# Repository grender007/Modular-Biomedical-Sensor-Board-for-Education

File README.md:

# Modular-Biomedical-Sensor-Board-for-Education (MediBrick-2000)
Modular Biomedical Sensor Board for Education (a.k.a. MediBrick-2000), designed for the Department of Biomedical Engineering (BME) of the University of Arizona (UofA). The device currently integrates five different sensor for physiological measurements:

* [Skin Impedance](https://github.com/grender007/Modular-Biomedical-Sensor-Board-for-Education/tree/main/Skin%20Impedance%20Sensor)

* [Temperature](https://github.com/grender007/Modular-Biomedical-Sensor-Board-for-Education/tree/main/Temperature%20Sensor)

* [ECG](https://github.com/grender007/Modular-Biomedical-Sensor-Board-for-Education/tree/main/ECG%20Sensor%20)

* [Pulse Ox ](https://github.com/grender007/Modular-Biomedical-Sensor-Board-for-Education/tree/main/Pulse%20Ox%20Sensor)

* [Digital Stethoscope](https://github.com/grender007/Modular-Biomedical-Sensor-Board-for-Education/tree/main/Sound%20Sensor)

Each one of the folders include the Arduino Code (that also enables wireless communication), the PCB files, and the corresponding insert for the casing.

# Project Point Design
This is a wireless device mainly supported by ESPNow. Each one of the sensors has its own PCB and its own ESP32-S3 (see Arduino Code in any of the sensor folders). The signals are sent to a sixth ESP32-S3, [the receiver](https://github.com/grender007/Modular-Biomedical-Sensor-Board-for-Education/tree/main/ESP32%20Receiver), that simultaneously communicates with the user's computer through the [GUI](https://github.com/grender007/Modular-Biomedical-Sensor-Board-for-Education/tree/main/GUI). The GUI displays the measurements in real time and allows the user to record and save the information.

When not in use, the sensors can be placed on the charging station, where the batteries can be recharged.

# Sensor Modules
All the sensor modules are meant to be the same, being the only difference each sensor and the PCB that includes the required circuitry (But all the PCB have the same dimension and orientation). Each [sensor module](https://github.com/grender007/Modular-Biomedical-Sensor-Board-for-Education/tree/main/Housing%20Models/Module%20Casing) has different features. It includes an OLED screen that displays the current battery level and a button that allows the deep sleep mode of the ESP32-S3. The casing it is designed for the ESP32-S3 to be powered by a battery and to recharge with a magnetic plug.
All the modules can be placed on the [charging station](https://github.com/grender007/Modular-Biomedical-Sensor-Board-for-Education/tree/main/Housing%20Models/Charging%20Station) to recharge the batteries. Similarly, the receiver includes its own [casing](https://github.com/grender007/Modular-Biomedical-Sensor-Board-for-Education/tree/main/Housing%20Models/Receiver%20Casing).

# Assembly
The detailed asssembly process and the required parts for the device are described in the [Documents folder](https://github.com/grender007/Modular-Biomedical-Sensor-Board-for-Education/tree/main/User%20Manual%20and%20Other%20Documents), as well other related documents like the Technical Data Package (TDP).

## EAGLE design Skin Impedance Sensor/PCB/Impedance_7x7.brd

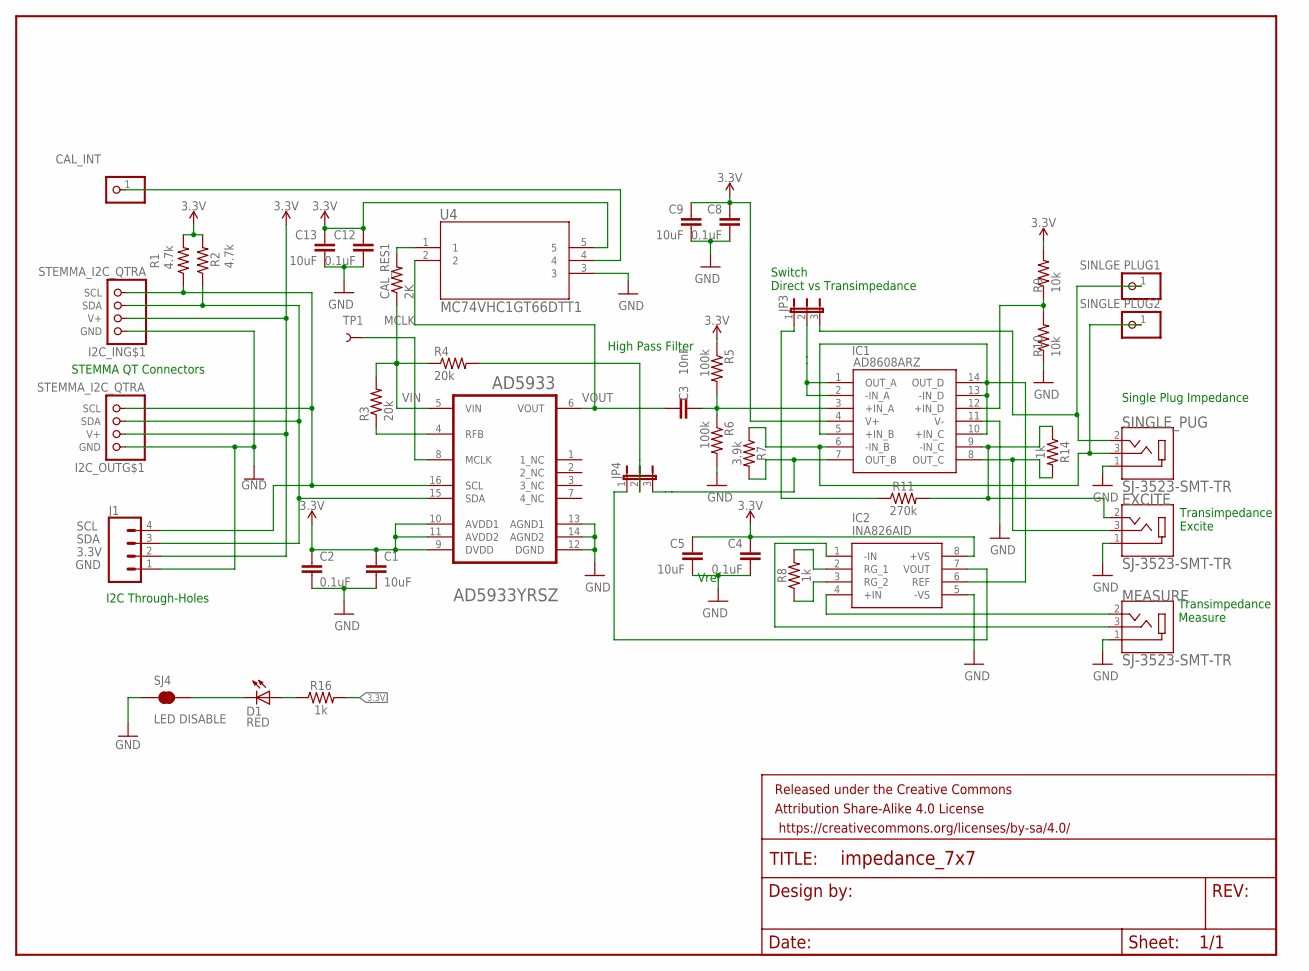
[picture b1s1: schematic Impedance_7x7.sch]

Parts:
AD5933: ANALOG_DEVICES_AD5933YRSZANALOG_DEVICES_AD5933YRS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; ANALOG_DEVICES_AD5933YRSZ_0
C1, C5, C9, C13: 10uF; C0603
C2, C4, C8, C12: 0.1uF; C0603
C3: 10nF; 0603
CAL_INT: PINHD-1X1; 1X01
CAL_RES1: 2K; R0603
D1: RED; LED-0603
EXCITE: SJ-3523-SMT-TR; CUI_SJ-3523-SMT-TR
FRAME1: FRAME-LETTERNO_PACKAGE; DUMMY
I2C_IN, I2C_OUT: STEMMA_I2C_QTRA; JST_SH4_RA
IC1: AD8608ARZ; SOIC127P600X175-14N
IC2: INA826AID; SOIC127P600X175-8N
J1: CONN_04; 1X04
JP3, JP4: JP2E; JP2
MEASURE: SJ-3523-SMT-TR; CUI_SJ-3523-SMT-TR
R1, R2: 4.7k; 0603
R3, R4: 20k; 0603
R5, R6: 100k; 0603
R7: 3.9k; 0603
R8, R14, R16: 1k; 0603
R9, R10: 10k; 0603
R11: 270k; 0603
SINGLE_PLUG1: SINLGE PLUG1; 1X01
SINGLE_PLUG2: SINGLE PLUG2; 1X01
SINGLE_PUG: SJ-3523-SMT-TR; CUI_SJ-3523-SMT-TR
SJ4: LED DISABLE; SMT-JUMPER_2_NC_TRACE_NO-SILK
TP1: TEST-POINT3X5; PAD.03X.05
U4: MC74VHC1GT66DTT1; TSOP5_1P65X3P15_ONS

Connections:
3.3V: AD5933.9 (DVDD), AD5933.10 (AVDD1), AD5933.11 (AVDD2), C1.1, C2.1, C4.1, C5.1, C8.1, C9.1, C12.1, C13.1, I2C_IN.2 (V+), I2C_OUT.2 (V+), IC1.4 (V+), IC2.8 (+VS), J1.2, R1.2, R2.2, R5.1, R9.2, R16.2, U4.5
GND: AD5933.12 (DGND), AD5933.13 (AGND1), AD5933.14 (AGND2), C1.2, C2.2, C4.2, C5.2, C8.2, C9.2, C12.2, C13.2, EXCITE.1, I2C_IN.1 (GND), I2C_OUT.1 (GND), IC1.11 (V-), IC2.5 (-VS), J1.1, MEASURE.1, R6.2, R10.1, SINGLE_PUG.1, SJ4.1, U4.3
MCLK: AD5933.8 (MCLK), TP1.P$1
unnamed: IC1.6 (-IN_B), R7.1, SINGLE_PLUG2.1, SINGLE_PUG.3
unnamed: CAL_INT.1, U4.4
unnamed: IC1.7 (OUT_B), JP4.3, R7.2
unnamed: JP4.2, R4.2
unnamed: AD5933.4 (RFB), R3.1
unnamed: C3.2, IC1.3 (+IN_A), R5.2, R6.1
unnamed: JP3.3, SINGLE_PLUG1.1, SINGLE_PUG.2
unnamed: JP3.1, R11.1
unnamed: IC1.1 (OUT_A), IC1.2 (-IN_A), JP3.2
unnamed: IC2.7 (VOUT), JP4.1
unnamed: IC1.12 (+IN_D), R9.1, R10.2
unnamed: IC1.5 (+IN_B), IC1.10 (+IN_C), IC1.13 (-IN_D), IC1.14 (OUT_D), IC2.6 (REF)
unnamed: EXCITE.2, IC1.9 (-IN_C), R11.2, R14.1
unnamed: IC2.4 (+IN), MEASURE.2
unnamed: IC2.1 (-IN), MEASURE.3
unnamed: IC2.2 (RG_1), R8.2
unnamed: IC2.3 (RG_2), R8.1
unnamed: CAL_RES1.2, U4.1
unnamed: EXCITE.3, IC1.8 (OUT_C), R14.2
unnamed: D1.A, R16.1
unnamed: D1.C, SJ4.2
SCL: AD5933.16 (SCL), I2C_IN.4 (SCL), I2C_OUT.4 (SCL), J1.4, R1.1
SDA: AD5933.15 (SDA), I2C_IN.3 (SDA), I2C_OUT.3 (SDA), J1.3, R2.1
VIN: AD5933.5 (VIN), CAL_RES1.1, R3.2, R4.1
VOUT: AD5933.6 (VOUT), C3.1, U4.2

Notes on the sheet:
High Pass Filter
Vref
Transimpedance Measure
Transimpedance Excite
Single Plug Impedance
STEMMA QT Connectors
I2C Through-Holes
Switch Direct vs Transimpedance

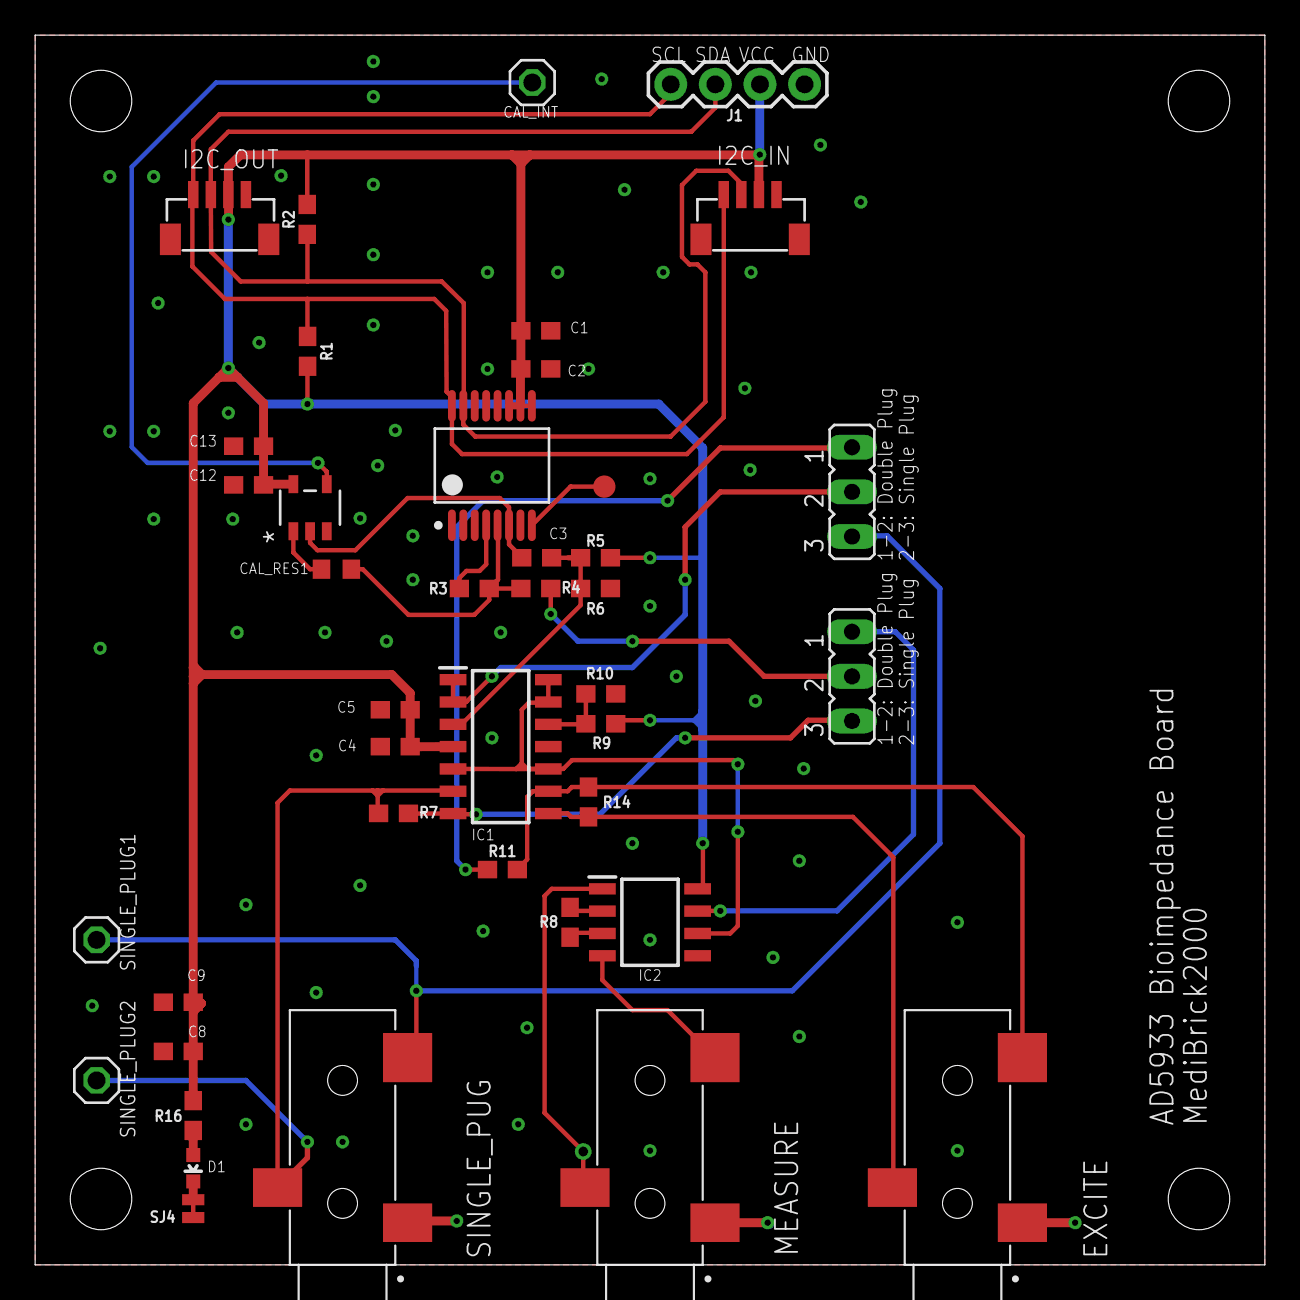
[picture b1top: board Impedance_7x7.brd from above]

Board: 2 copper layers, 70.0 x 70.0 mm, 42 parts (0 on the bottom side), 28 nets.

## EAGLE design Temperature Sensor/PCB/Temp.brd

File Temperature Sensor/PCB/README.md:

The temperature PCB is the simplest PCB of this project. It opperates using a simple wheatstone bridge, a parallel circuit composed of two branches, each with two resistors on each branch. One resistor is a thermistor, a resistor whose resistance changes with the temperature, serving as the probe for the project. As the temperature and thus resistance of the probe changes, the reading between the resistors of both branches will change. This difference in voltage is measured by the ESP32 and is used to calculate the temperature of the thermistor.

The PCB is also outfitted with a Red LED, allowing the User to see when the PCB has power.

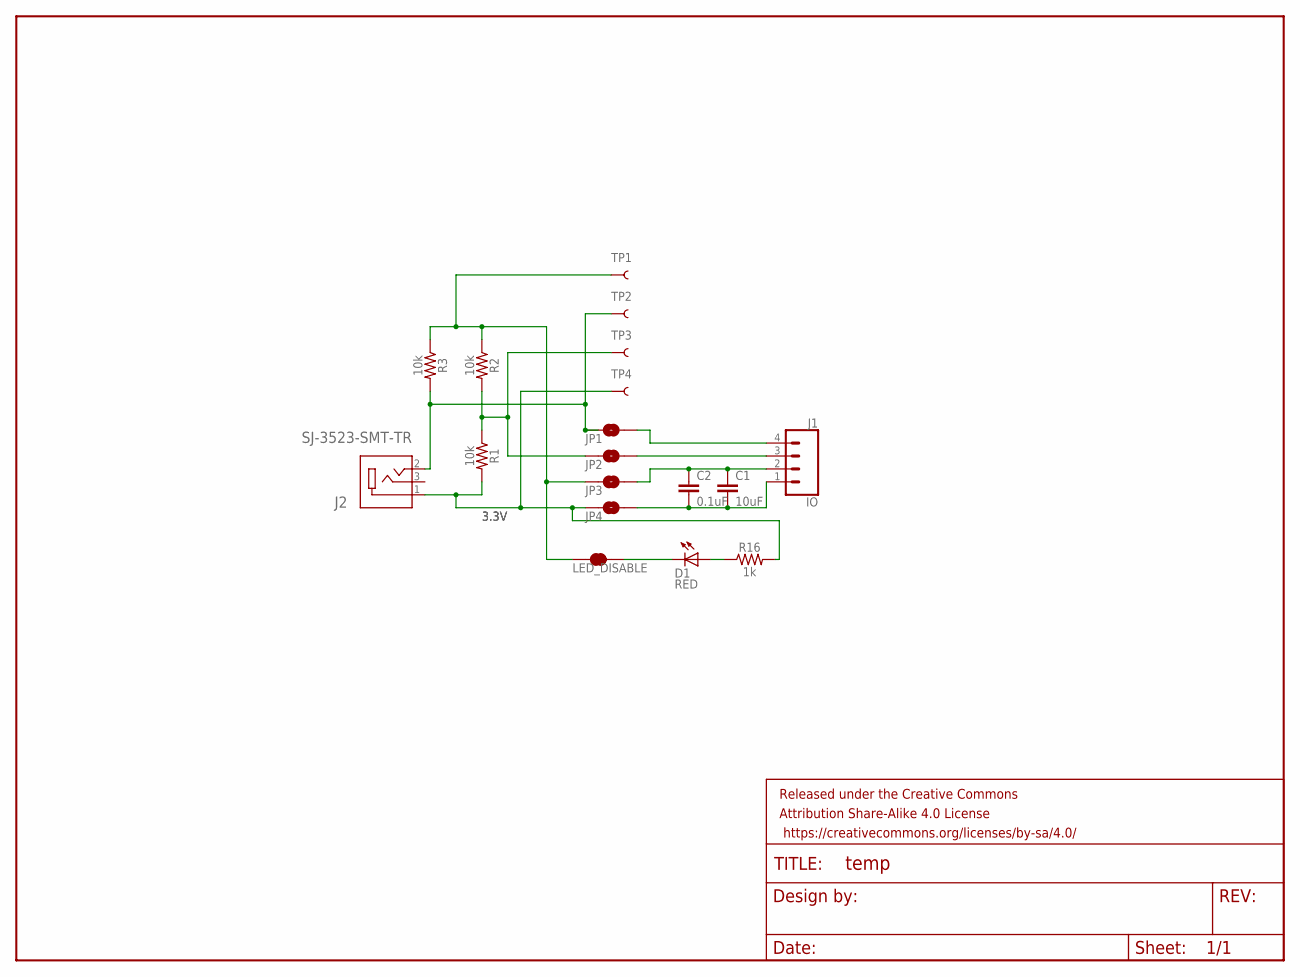
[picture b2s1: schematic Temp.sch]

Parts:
C1: 10uF; 0603
C2: 0.1uF; 0603
D1: RED; LED-0603
FRAME1: FRAME-LETTERNO_PACKAGE; DUMMY
J1: IO; 1X04
J2: SJ-3523-SMT-TR; CUI_SJ-3523-SMT-TR
JP1, JP2, JP3, JP4: JUMPER-SMT_2_NO_NO-SILK; SMT-JUMPER_2_NO_NO-SILK
LED_DISABLE: JUMPER-SMT_2_NC_TRACE_SILK; SMT-JUMPER_2_NC_TRACE_SILK
R1, R2, R3: 10k; 0603
R16: 1k; 0603
TP1, TP2, TP3, TP4: TEST-POINT3X5; PAD.03X.05

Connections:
3.3V: J2.1, JP4.1, R1.2, R16.2, TP4.P$1
unnamed: JP3.1, LED_DISABLE.1, R2.1, R3.1, TP1.P$1
unnamed: C1.2, C2.2, J1.1, JP4.2
unnamed: JP2.1, R1.1, R2.2, TP3.P$1
unnamed: C1.1, C2.1, J1.2, JP3.2
unnamed: J1.3, JP2.2
unnamed: J2.2, JP1.1, R3.2, TP2.P$1
unnamed: J1.4, JP1.2
unnamed: D1.A, R16.1
unnamed: D1.C, LED_DISABLE.2

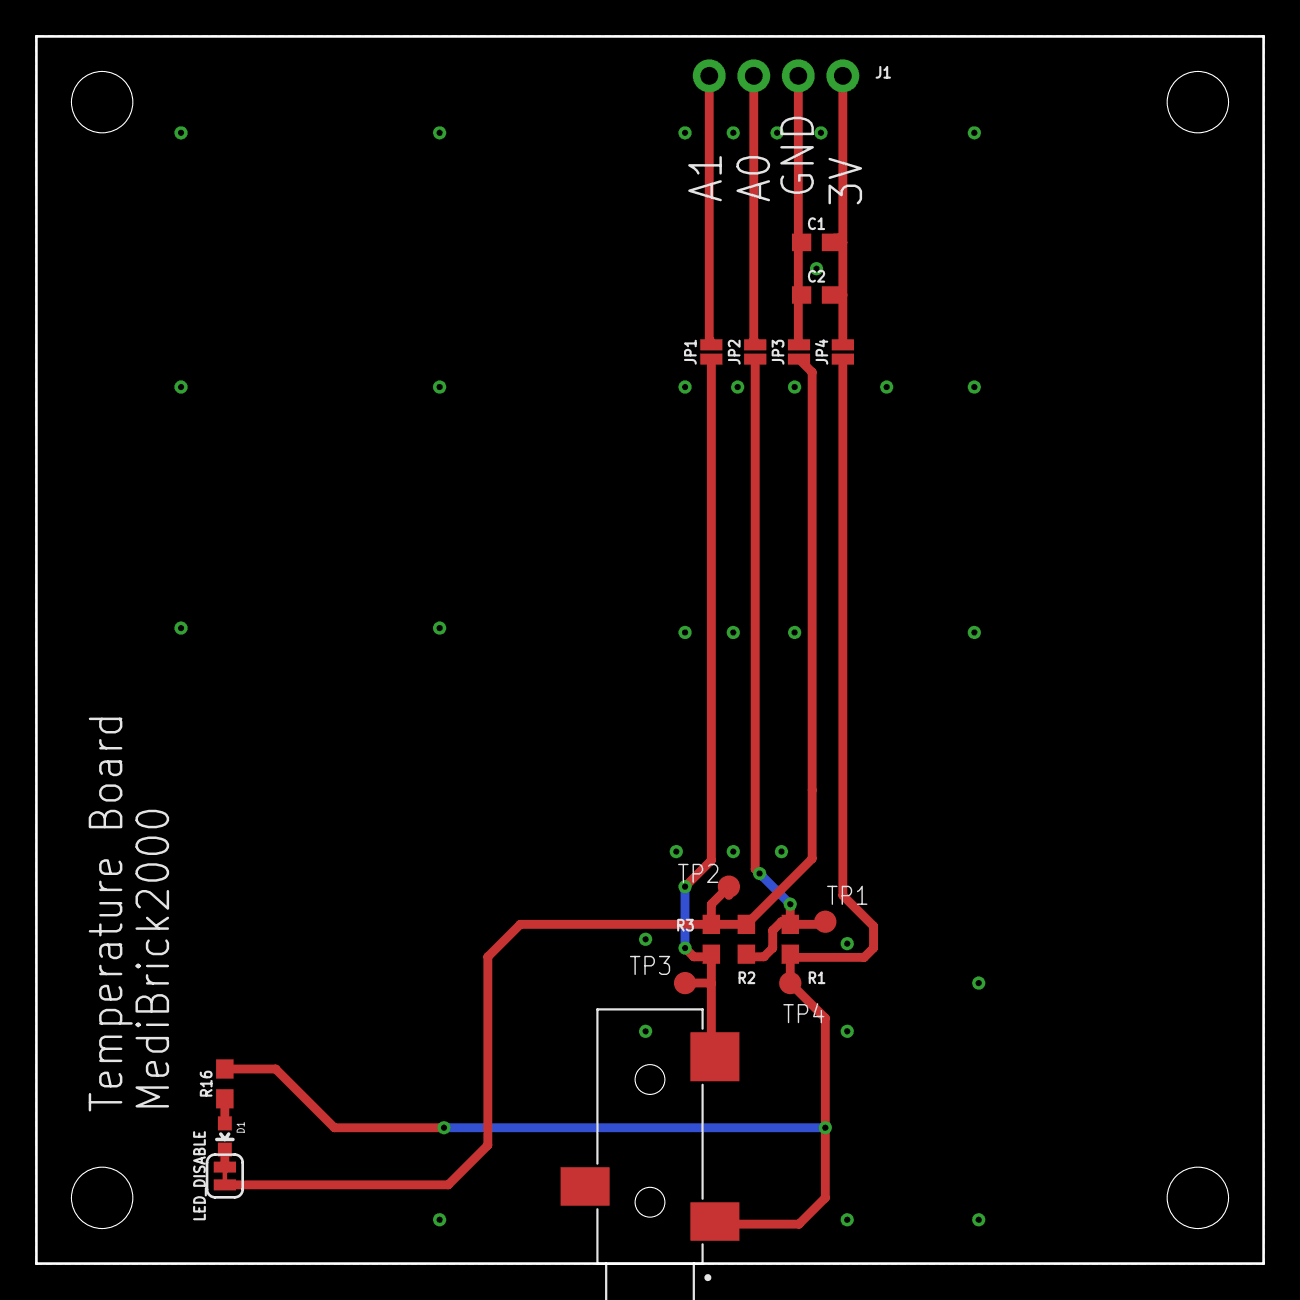
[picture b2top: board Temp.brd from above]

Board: 2 copper layers, 70.0 x 70.0 mm, 19 parts (1 on the bottom side), 10 nets.

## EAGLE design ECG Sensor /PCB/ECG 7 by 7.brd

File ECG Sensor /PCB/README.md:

Similar to the other sensors the ECG is a 70 mm x 70 mm board. This board was developed using EAGLE. The design is very simple. It has a slot that perfectly fits a Sparkfun ECG Pre-amplifier board. Pinholes are added to the walls of the board for easier wiring. This board also has an led as an indication of proper connection.

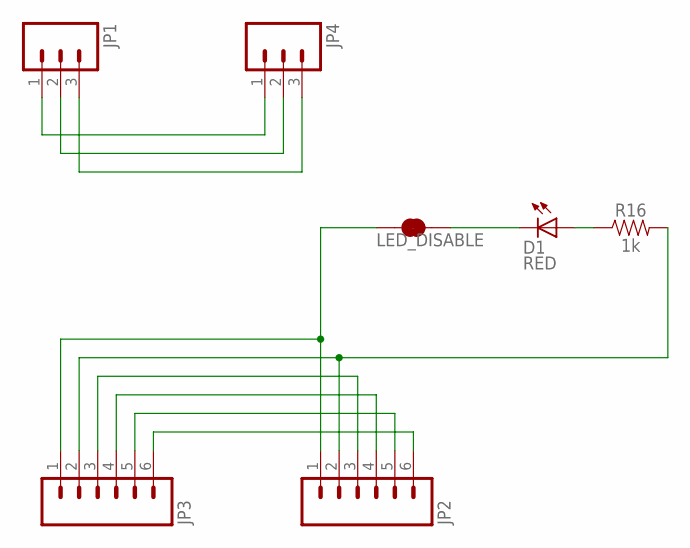
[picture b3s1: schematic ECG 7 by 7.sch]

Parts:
D1: RED; LED-0603
JP1, JP4: M03PTH; 1X03
JP2, JP3: M06SIP; 1X06
LED_DISABLE: JUMPER-SMT_2_NC_TRACE_SILK; SMT-JUMPER_2_NC_TRACE_SILK
R16: 1k; 0603

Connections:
unnamed: JP1.1, JP4.1
unnamed: JP1.2, JP4.2
unnamed: JP1.3, JP4.3
unnamed: JP2.6, JP3.6
unnamed: JP2.5, JP3.5
unnamed: JP2.4, JP3.4
unnamed: JP2.3, JP3.3
unnamed: JP2.2, JP3.2, R16.2
unnamed: JP2.1, JP3.1, LED_DISABLE.1
unnamed: D1.A, R16.1
unnamed: D1.C, LED_DISABLE.2

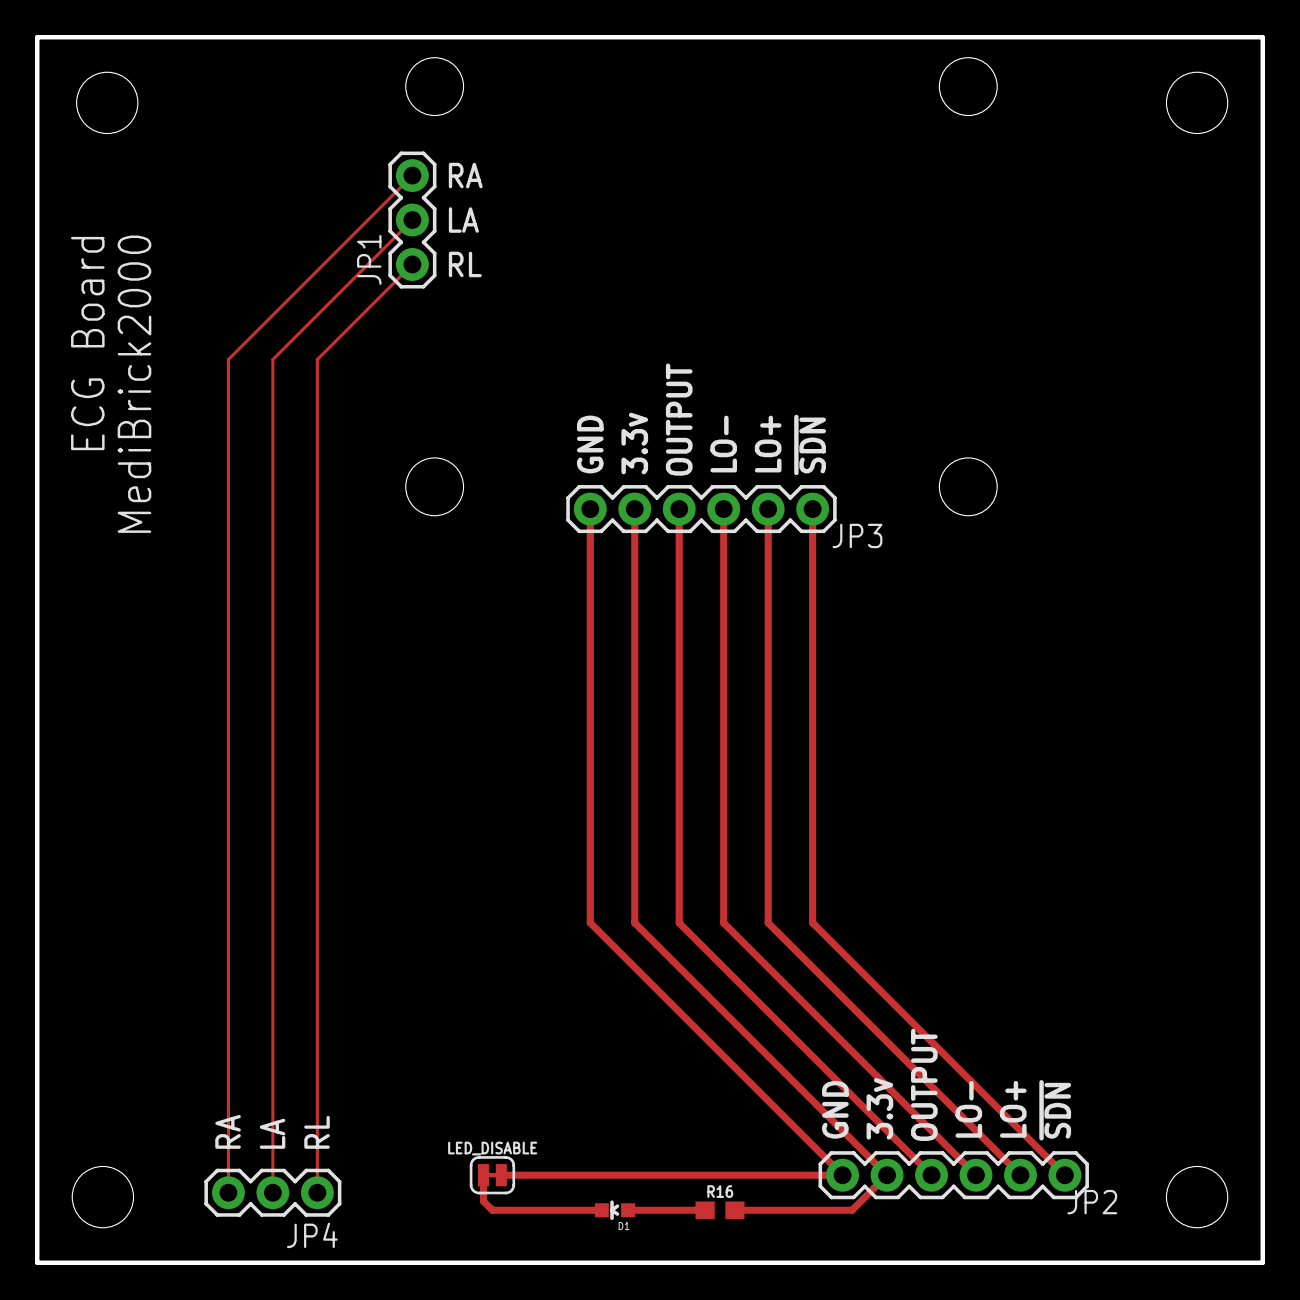
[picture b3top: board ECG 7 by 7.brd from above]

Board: 2 copper layers, 70.0 x 70.0 mm, 11 parts (0 on the bottom side), 11 nets.

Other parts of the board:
STANDOFF1, STANDOFF2, STANDOFF3, STANDOFF4: STAND-OFF

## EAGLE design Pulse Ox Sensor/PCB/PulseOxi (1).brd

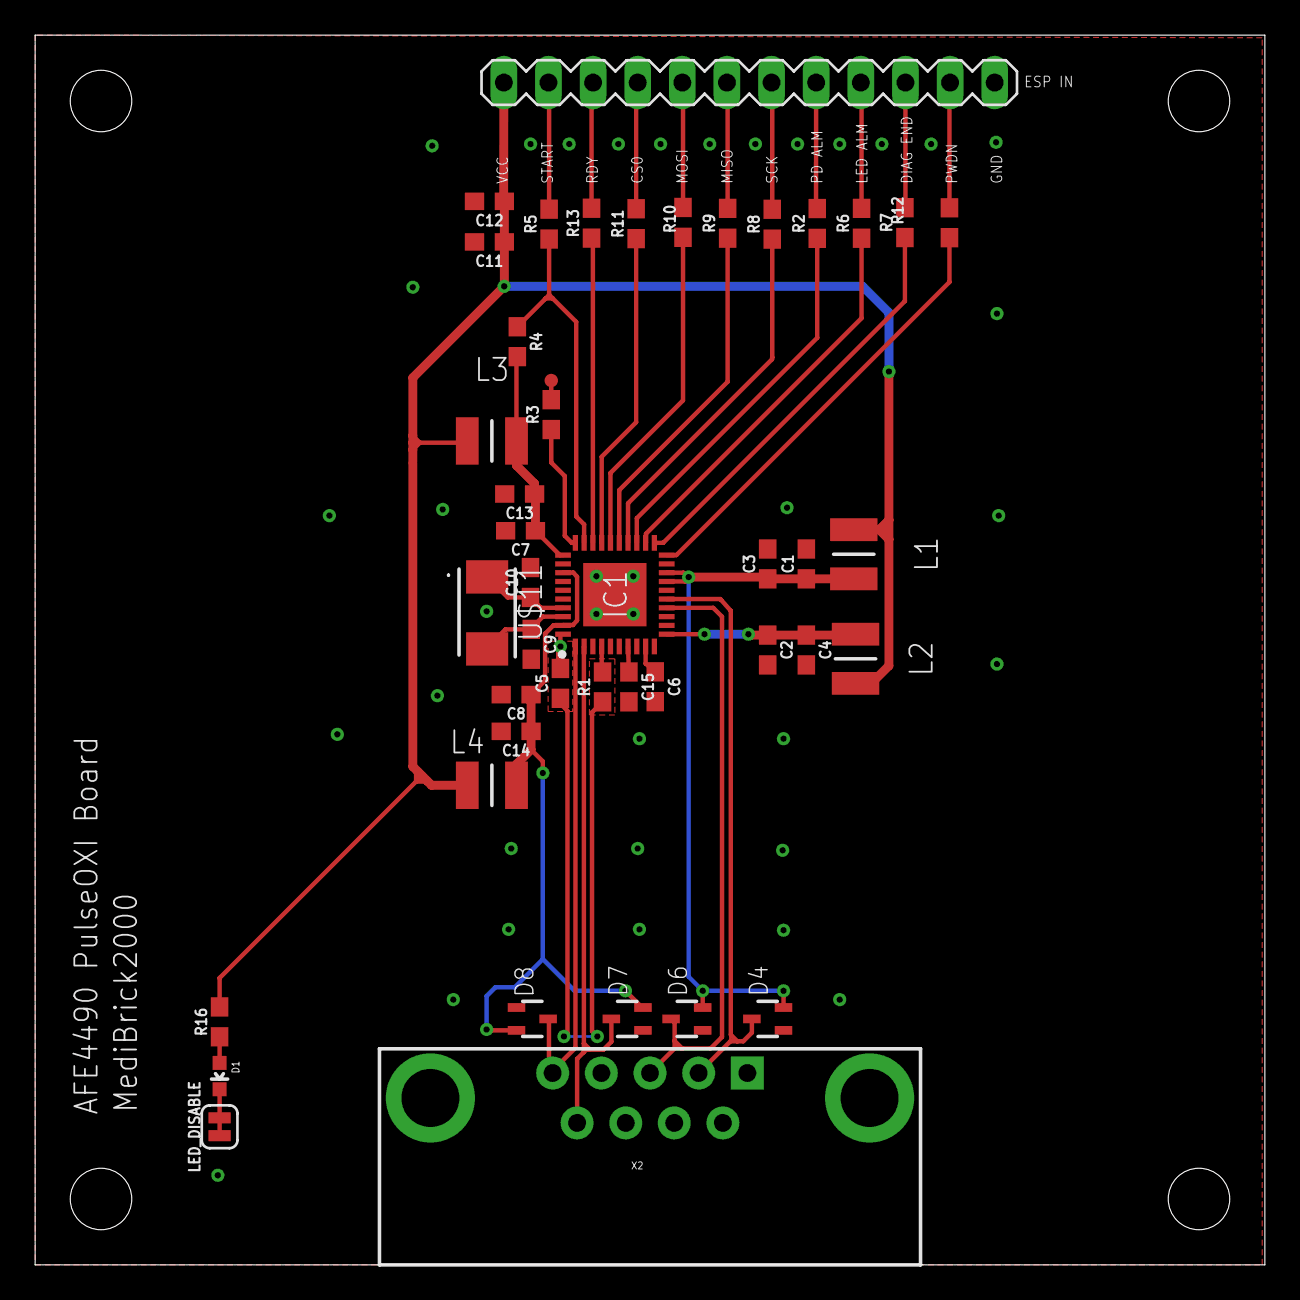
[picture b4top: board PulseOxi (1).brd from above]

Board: 2 copper layers, 70.0 x 70.0 mm, 45 parts (0 on the bottom side), 40 nets.

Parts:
C1, C2, C12, C13, C14: 10uF; 0603
C3: 1uF; 0603
C4, C7, C8: 0.1uF; 0603
C5: 10nF; 0603
C6, C15: 2.2uF; 0603
C9, C10: 18pF; 0603
C11: 100nF; 0603
D1: RED; LED-0603
D4, D6, D7, D8: SOT323
FRAME1: FRAME-LETTERNO_PACKAGE; DUMMY
IC1: AFE4400RHAR; QFN50P600X600X100-41N
L1, L2, L3, L4: LBC3225T100KR; INDC3225X270N
LED_DISABLE: JUMPER-SMT_2_NC_TRACE_SILK; SMT-JUMPER_2_NC_TRACE_SILK
R1, R16: 1k; 0603
R2, R3, R5, R6, R7, R8, R9, R10, R11, R12, R13: 10R; 0603
R4: 10k; 0603
SV1: MA12-1
TP2: TEST-POINT3; PAD.03X.03
U$11: ABM3-8.000MHZ-D2Y-T; ABM3
X2: DB9

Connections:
ADCRDY: R13.2, SV1.3
AFE_PWDN: IC1.20, R12.1
CS: R11.2, SV1.4
DIAGEND: R7.2, SV1.10
GND: C1.2, C2.2, C3.2, C4.2, C5.2, C6.2, C7.2, C8.2, C9.2, C10.2, C11.2, C12.2, C13.2, C14.2, C15.2, D4.2, D6.2, D7.2, D8.2, IC1.3, IC1.8, IC1.12, IC1.13, IC1.16, IC1.19, IC1.32, IC1.36, IC1.40, IC1.41, LED_DISABLE.1, SV1.12, X2.7, X2.G1, X2.G2
INN: D8.1, IC1.1, X2.5
INP: D7.1, IC1.2, X2.9
LEDALARM: R6.2, SV1.9
LED_DRV_SUP: C1.1, C3.1, D4.3, D6.3, IC1.17, IC1.18, L1.2
MISO: R9.2, SV1.6
MOSI: R10.2, SV1.5
unnamed: R3.2, TP2.P$1
unnamed: IC1.30, R3.1
unnamed: IC1.29, R4.1, R5.1
unnamed: C15.1, IC1.7
unnamed: C5.1, R1.1
unnamed: C6.1, IC1.9
unnamed: IC1.28, R13.1
unnamed: IC1.21, R7.1
unnamed: IC1.22, R6.1
unnamed: IC1.23, R2.1
unnamed: IC1.24, R8.1
unnamed: IC1.25, R9.1
unnamed: IC1.26, R10.1
unnamed: IC1.27, R11.1
unnamed: C9.1, IC1.38, U$11.2
unnamed: IC1.4, R1.2
unnamed: C10.1, IC1.37, U$11.1
unnamed: D1.A, R16.1
unnamed: D1.C, LED_DISABLE.2
PD_ALM_OUT: R2.2, SV1.8
PWDN: R12.2, SV1.11
RESET: R5.2, SV1.2
RX_ANA_SUP: C8.1, C14.1, D7.3, D8.3, IC1.33, IC1.39, L4.2
RX_DIG_SUP: C7.1, C13.1, IC1.31, L3.2, R4.2
SCK: R8.2, SV1.7
TXN: D6.1, IC1.14, X2.3
TXP: D4.1, IC1.15, X2.2
TX_CTRL_SUP: C2.1, C4.1, IC1.11, L2.2
VCC: C11.1, C12.1, L1.1, L2.1, L3.1, L4.1, R16.2, SV1.1

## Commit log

2024-04-25 Add files via upload
    ECG ESP32 Sender Code
2024-04-29 Update and rename Readme to README
2024-05-03 Add files via upload
    Pulse ox code for medibrick2000
2024-05-03 Add files via upload
    bill of materials

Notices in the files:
parts and their libraries:
SparkFun-Connectors: Licensing: CC v3.0 Share-Alike You are welcome to use this library for commercial purposes.
SparkFun-Resistors: Licensing: Creative Commons ShareAlike 4.0 International - https://creativecommons.org/licenses/by-sa/4.0
SparkFun-Aesthetics: Released under the Creative Commons
